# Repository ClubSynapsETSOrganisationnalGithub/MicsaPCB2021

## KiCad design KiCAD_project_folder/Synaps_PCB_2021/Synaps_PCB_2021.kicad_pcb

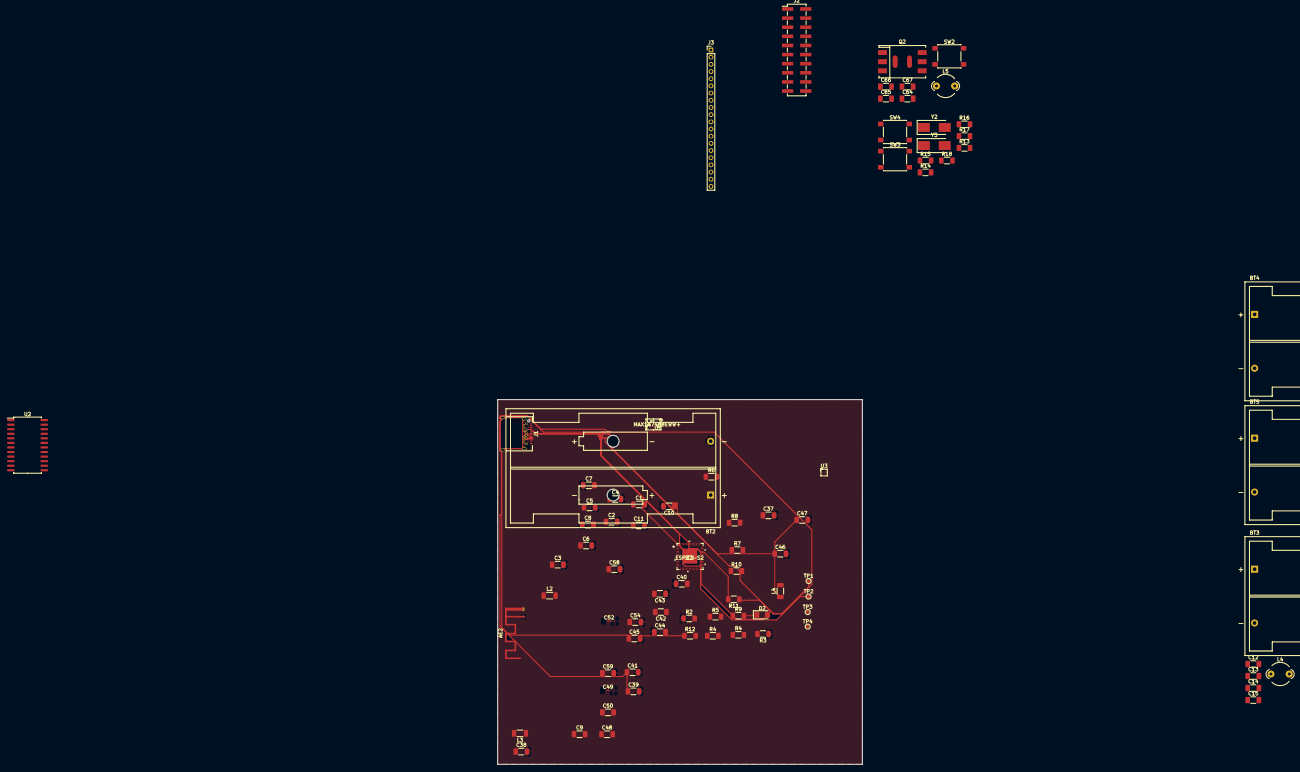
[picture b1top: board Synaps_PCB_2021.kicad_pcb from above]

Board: 4 copper layers, 101.6 x 101.6 mm, 83 parts (0 on the bottom side), 88 nets.

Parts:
AE2: PBC ANT; Texas_SWRA117D_2.4GHz_Left
BT2, BT3, BT4, BT5: Battery_Cell; BatteryHolder_Keystone_2462_2xAA
C1, C6, C40, C44, C45: 1uF; C_1206_3216Metric_Pad1.33x1.80mm_HandSolder
C2, C3, C4, C13, C15, C38, C41, C42, C46, C65, C66: 0.1uF; C_1206_3216Metric_Pad1.33x1.80mm_HandSolder
C5: 100pF; C_1206_3216Metric_Pad1.33x1.80mm_HandSolder
C7, C8: 22pF; C_1206_3216Metric_Pad1.33x1.80mm_HandSolder
C9: 1µF; C_1206_3216Metric_Pad1.33x1.80mm_HandSolder
C10, C11: 0.1uF/50V(10%)(NC); C_1206_3216Metric_Pad1.33x1.80mm_HandSolder
C12, C14, C39, C47, C64, C67: 10uF; C_1206_3216Metric_Pad1.33x1.80mm_HandSolder
C37: 22uF; C_1206_3216Metric_Pad1.33x1.80mm_HandSolder
C43: 3.9nF; C_1206_3216Metric_Pad1.33x1.80mm_HandSolder
C48: 10µF; C_1206_3216Metric_Pad1.33x1.80mm_HandSolder
C49: 19pF; C_01005_0402Metric
C50: 0.1µF; C_1206_3216Metric_Pad1.33x1.80mm_HandSolder
C52: 16pF; C_01005_0402Metric_Pad0.57x0.30mm_HandSolder
C54: NC; C_1206_3216Metric_Pad1.33x1.80mm_HandSolder
C58, C59: 22pF/6.3V(10%); C_1206_3216Metric_Pad1.33x1.80mm_HandSolder
D2: LED; LED_1206_3216Metric_Pad1.42x1.75mm_HandSolder
IC2: ESP32-S2
J1: USB_C_Receptacle; USB_C_Receptacle_Amphenol_12401548E4-2A
J2: Conn_02x10_MountingPin; PinHeader_2x10_P2.54mm_Vertical_SMD
J3: Conn_01x20_MountingPin; PinHeader_1x20_P2.00mm_Vertical
L2: 0.5028nH; L_1206_3216Metric_Pad1.22x1.90mm_HandSolder
L3: 2.0nH; L_1206_3216Metric_Pad1.22x1.90mm_HandSolder
L4, L5: L_Ferrite 60 Omh 1.5 A; LairdTech_28C0236-0JW-10
L4#2: INDUCTOR; L_1206_3216Metric_Pad1.22x1.90mm_HandSolder
Q2: Q_PMOS_DGS; Transformer_NF_ETAL_P2781
R2, R6, R11: 10K; R_1206_3216Metric_Pad1.30x1.75mm_HandSolder
R3: 1M; R_1206_3216Metric_Pad1.30x1.75mm_HandSolder
R4, R4#2, R5, R10, R12: 4.7K; R_1206_3216Metric_Pad1.30x1.75mm_HandSolder
R7, R8, R13, R14, R15, R16: 0; R_1206_3216Metric_Pad1.30x1.75mm_HandSolder
R9: 1K; R_1206_3216Metric_Pad1.30x1.75mm_HandSolder
R17: 499; R_1206_3216Metric_Pad1.30x1.75mm_HandSolder
R18: 10M; R_1206_3216Metric_Pad1.30x1.75mm_HandSolder
SW2, SW3, SW4: SW_Push; SW_Push_1P1T_NO_6x6mm_H9.5mm
TP1: TPCC1; TestPoint_Pad_D1.0mm
TP2: TPCC2; TestPoint_Pad_D1.0mm
TP3: TPCDN; TestPoint_Pad_D1.0mm
TP4: TPCDP; TestPoint_Pad_D1.0mm
U1: MAX14748BEWW+; MAX14748BEWW&plus_
U2: CD74HC4067M; SOIC-24W_7.5x15.4mm_P1.27mm
U3: AT25DF041x-UxN-x; WLCSP-8_1.58x1.63x0.35mm_Layout3x5_P0.35x0.4mm_Ball0.25mm_P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
Y2: 40 MHz; Crystal_SMD_0603-2Pin_6.0x3.5mm_HandSoldering
Y3: 32.768 KHz; Crystal_SMD_0603-2Pin_6.0x3.5mm_HandSoldering

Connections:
+1V1: C2.1, C3.1, C4.1, C5.1, C6.1, C9.1, C37.1, C38.1, C48.1, C50.1, C64.1, C65.1, IC2.1 (VDDA), IC2.20 (VDD3P3_RTC), IC2.27 (VDD3P3_RTC_IO), IC2.45 (VDD3P3_CPU), IC2.51 (VDDA), IC2.54 (VDDA), J3.1, L3.1, L5.1, R4.2, R4#2.2, R5.2, R6.2, R10.1, R12.2, SW2.2, U1.B4 (VTPU), U1.B6 (SYS), U1.B7 (SYS), U1.B8 (SYS), U1.B9 (SYS), U2.24 (VCC)
+5V: C12.1, C13.1, L4.1
/Connectors/CAN_BUS_CLK: IC2.15 (GPIO10), J2.4
/Connectors/CAN_BUS_OFF_ON: IC2.14 (GPIO9), J2.5
/Connectors/CAN_BUS_RX: IC2.12 (GPIO7), J2.2
/Connectors/CAN_BUS_TX: IC2.13 (GPIO8), J2.3
/Connectors/GPIO11: IC2.16 (GPIO11), IC2.28 (GPIO21), J2.15, J2.16
/Connectors/JTAG_MTCK: IC2.43 (MTCK), J2.13
/Connectors/JTAG_MTDI: IC2.47 (MTMS), J2.11
/Connectors/JTAG_MTDO: IC2.44 (MTDO), J2.12
/Connectors/JTAG_MTMS: IC2.46 (MTDI), J2.10
/Connectors/U0RXD: IC2.49 (U0RXD), J2.18
/Connectors/U0TXD: J2.19, R17.2
/Microcontroler/*INT: IC2.7 (GPIO2), R4.1, R4#2.1, R5.1, U1.A3 (SYSOK), U1.D3 (*INT)
/Microcontroler/ADC2_CH1: IC2.18 (GPIO13), IC2.19 (GPIO14)
/Microcontroler/CHIP_BOOT: C10.1, SW3.2
/Microcontroler/CHIP_PU: C11.1, IC2.56 (CHIP_PU), SW4.2
/Microcontroler/DAC_2: IC2.24 (DAC_2), R6.1
/Microcontroler/FSUS: IC2.17 (GPIO12), U1.B2 (FSUS)
/Microcontroler/I2CEXT0_SCL_out: IC2.9 (GPIO4), R10.2, R12.1, U1.C2 (SCL), U1.D2 (SDA)
/Microcontroler/LED_PMIC: D2.2 (A), IC2.11 (GPIO6), R9.1, U1.E2 (LED)
/Microcontroler/LNA_IN: C52.1, IC2.2 (LNA_IN), L2.2
/Microcontroler/SPI3_CLK: IC2.41 (GPIO37), J3.20
/Microcontroler/SPI3_CS0: IC2.40 (GPIO36), U2.10 (S0)
/Microcontroler/SPI3_CS1: IC2.37 (GPIO33), U2.11 (S1)
/Microcontroler/SPI3_CS2: IC2.42 (GPIO38), U2.14 (S2)
/Microcontroler/SPI3_MISO: IC2.38 (GPIO34), U2.1 (COM)
/Microcontroler/SPI3_MOSI: IC2.39 (GPIO35), J3.3
/Microcontroler/SPICLK: R13.2, U3.E1 (SCK)
/Microcontroler/SPICS0: IC2.33 (SPIS0), U3.A3 (~CS)
/Microcontroler/SPID: R7.2, U3.D2 (SI/IO0)
/Microcontroler/SPIQ: R8.2, U3.C3 (SO/IO1)
/Microcontroler/SPIWP: R14.2, U3.E3 (~WP)
/Microcontroler/USB_D+: IC2.26 (GPIO20), J1.A6 (D+), J1.B6 (D+), TP4.1
/Microcontroler/USB_D-: IC2.25 (GPIO19), J1.A7 (D-), J1.B7 (D-), TP3.1
/Microcontroler/VDD3P3: C54.1, IC2.3 (VDD3P3), IC2.4 (VDD3P3), L3.2
/Microcontroler/VDD_SPI: IC2.30 (VDD_SPI), U3.A1 (VCC)
/Microcontroler/XIN: C58.1, R16.2, Y2.1
/Microcontroler/XOUT: C59.1, IC2.52 (XTAL_N)
/Microcontroler/XTAL_32K_N: C8.2, IC2.22 (XTAL_32K_N), R18.2, Y3.2
/Microcontroler/XTAL_32K_P: C7.2, IC2.21 (XTAL32K_P), R18.1, Y3.1
/Microcontroler/XTAL_P: IC2.53 (XTAL_P), R16.1
/Power Supply/CC1: J1.A5 (CC1), TP1.1, U1.D1 (CC1)
/Power Supply/CC2: J1.B5 (CC2), TP2.1
/Power Supply/LX: C42.1, L4#2.2, U1.C6 (LX), U1.C7 (LX), U1.C8 (LX), U1.C9 (LX)
/Power Supply/TPU: R11.2, U1.E3 (THM)
/Power Supply/V_BAT: BT3.1 (+), C39.1, C41.1, SW2.1, U1.A7 (BAT), U1.A8 (BAT), U1.A9 (BAT)
/Probes schematic/SPI_CS_ADC0: J3.4, U2.9 (I0)
/Probes schematic/SPI_CS_ADC1: J3.6, U2.7 (I2)
/Probes schematic/SPI_CS_ADC2: J3.8, U2.5 (I4)
/Probes schematic/SPI_CS_ADC3: J3.10, U2.3 (I6)
/Probes schematic/SPI_CS_ADC4: J3.12, U2.23 (I8)
/Probes schematic/SPI_CS_ADC5: J3.14, U2.21 (I10)
/Probes schematic/SPI_CS_ADC6: J3.16, U2.19 (I12)
/Probes schematic/SPI_CS_ADC7: J3.18, U2.17 (I14)
/Probes schematic/SPI_OUT_ADC0: J3.5, U2.8 (I1)
/Probes schematic/SPI_OUT_ADC1: J3.7, U2.6 (I3)
/Probes schematic/SPI_OUT_ADC2: J3.9, U2.4 (I5)
/Probes schematic/SPI_OUT_ADC3: J3.11, U2.2 (I7)
/Probes schematic/SPI_OUT_ADC4: J3.13, U2.22 (I9)
/Probes schematic/SPI_OUT_ADC5: J3.15, U2.20 (I11)
/Probes schematic/SPI_OUT_ADC6: J3.17, U2.18 (I13)
/Probes schematic/SPI_OUT_ADC7: J3.19, U2.16 (I15)
GNDREF: AE2.1, BT2.2 (-), BT5.2 (-), C1.2, C2.2, C3.2, C4.2, C5.2, C6.2, C7.1, C8.1, C9.2, C10.2, C11.2, C12.2, C13.2, C14.2, C15.2, C37.2, C38.2, C39.2, C40.1, C41.2, C43.1, C44.1, C45.2, C46.2, C47.2, C48.2, C49.2, C50.2, C52.2, C54.2, C58.2, C59.2, C64.2, C65.2, C66.2, C67.2, IC2.57 (EPAD), J1.A1 (GND), J1.A12 (GND), J1.B1 (GND), J1.B12 (GND), J2.1, J2.6, J2.9, J2.14, J2.17, J2.20, J3.2, R2.1, R3.1, SW3.1, SW4.1, U1.B3 (DGND), U1.C4 (GND), U1.D4 (GND), U1.D5 (GND), U1.D6 (PGND), U1.D7 (PGND), U1.D8 (PGND), U1.D9 (PGND), U2.12 (GND), U2.15 (~E), U3.B2 (GND), Y2.2
unnamed: AE2.2, C49.1, L2.1
unnamed: BT2.1 (+), BT3.2 (-)
unnamed: BT4.2 (-), BT5.1 (+)
unnamed: C14.1, C15.1, L4.2
unnamed: C40.2, U1.C3 (VCCINT)
unnamed: C42.2, U1.C5 (BST)
unnamed: C43.2, U1.A5 (COMP)
unnamed: C44.2, U1.B5 (BREG)
unnamed: C45.1, U1.E4 (SFOUT)
unnamed: C46.1, C47.1, L4#2.1, U1.E6 (BYP), U1.E7 (BYP), U1.E8 (BYP), U1.E9 (BYP)
unnamed: D2.1 (K), R9.2
unnamed: IC2.34 (SPICLK), R13.1
unnamed: IC2.36 (SPID), R7.1
unnamed: IC2.31 (SPIHD), R15.1
unnamed: IC2.35 (SPIQ), R8.1
unnamed: IC2.32 (SPIWD), R14.1
unnamed: IC2.48 (U0TXD), R17.1
unnamed: J1.S1 (SHIELD), R3.2
unnamed: Q2.2 (G), U1.F5 (NVP)
unnamed: Q2.3 (S), U1.F6 (CHGIN), U1.F7 (CHGIN), U1.F8 (CHGIN), U1.F9 (CHGIN)
unnamed: R2.2, U1.A6 (SET)
unnamed: R11.1, U1.A4 (TPU)
VAA: C66.1, C67.1, L5.2
VBUS: C1.1, J1.A4 (VBUS), J1.A9 (VBUS), J1.B4 (VBUS), J1.B9 (VBUS)

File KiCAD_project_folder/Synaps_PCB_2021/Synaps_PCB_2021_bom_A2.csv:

Component;Description;Part;References;Value;Footprint;Quantity Per PCB;Datasheet;Supplier Link
1;Dipole antenna;Antenna_Dipole;AE2;PBC ANT;Texas_SWRA117D_2.4GHz_Left;1;~;
2;Single-cell battery;Battery_Cell;BT2;Battery_Cell;BatteryHolder_Keystone_2462_2xAA;1;~;
3;Unpolarized capacitor;C;C7 C8;12.5pF;C_1206_3216Metric_Pad1.33x1.80mm_HandSolder;2;~;
4;Unpolarized capacitor;C;C5;100pF;C_1206_3216Metric_Pad1.33x1.80mm_HandSolder;1;~;
5;Unpolarized capacitor;C;C43;3.9nF;C_1206_3216Metric_Pad1.33x1.80mm_HandSolder;1;~;
6;Unpolarized capacitor;C;C2 C3 C4 C38 C41 C42 C46 C50 C65 C66;0.1uF;C_1206_3216Metric_Pad1.33x1.80mm_HandSolder;10;~;
7;Capacitor symbol for simulation only;CAP;C1;1uF;C_1206_3216Metric_Pad1.33x1.80mm_HandSolder;1;~;
8;Unpolarized capacitor;C;C6 C9 C40 C44 C45;1uF;C_1206_3216Metric_Pad1.33x1.80mm_HandSolder;5;~;
9;Unpolarized capacitor;C;C39 C47 C48 C64 C67;10uF;C_1206_3216Metric_Pad1.33x1.80mm_HandSolder;5;~;
10;Unpolarized capacitor;C;C37;22uF;C_1206_3216Metric_Pad1.33x1.80mm_HandSolder;1;~;
11;Unpolarized capacitor;C;C10 C11;0.1uF/50V(10%)(NC);C_1206_3216Metric_Pad1.33x1.80mm_HandSolder;2;~;
12;Unpolarized capacitor;C;C58 C59;22pF/6.3V(10%);C_1206_3216Metric_Pad1.33x1.80mm_HandSolder;2;~;
13;Unpolarized capacitor;C;C54;NC;C_1206_3216Metric_Pad1.33x1.80mm_HandSolder;1;~;
14;Unpolarized capacitor;C;C49 C52;TBD;C_1206_3216Metric_Pad1.33x1.80mm_HandSolder;2;~;
15;Light emitting diode;LED;D2;LED;LED_1206_3216Metric_Pad1.42x1.75mm_HandSolder;1;~;
16;;ESP32-S2;IC2;ESP32-S2;ESP32-S2;1;;
17;Generic connectable mounting pin connector, single row, 01x20, script generated (kicad-library-utils/schlib/autogen/connector/);Conn_01x20_MountingPin;J2 J3;Conn_01x20_MountingPin;PinHeader_1x20_P2.00mm_Vertical;2;~;
18;USB Full-Featured Type-C Receptacle connector;USB_C_Receptacle;J1;USB_C_Receptacle;USB_C_Receptacle_Amphenol_12401548E4-2A;1;https://www.usb.org/sites/default/files/documents/usb_type-c.zip;
19;Inductor symbol for simulation only;INDUCTOR;L3;2.0nH;L_1206_3216Metric_Pad1.22x1.90mm_HandSolder;1;~;
20;Inductor symbol for simulation only;INDUCTOR;L4;INDUCTOR;L_1206_3216Metric_Pad1.22x1.90mm_HandSolder;1;~;
21;Inductor with ferrite core;L_Ferrite;L5;L_Ferrite;LairdTech_28C0236-0JW-10;1;~;
22;Inductor symbol for simulation only;INDUCTOR;L2;TBD;L_1206_3216Metric_Pad1.22x1.90mm_HandSolder;1;~;
23;P-MOSFET transistor, drain/gate/source;Q_PMOS_DGS;Q2;Q_PMOS_DGS;Transformer_NF_ETAL_P2781;1;~;
24;Resistor, US symbol;R_US;R7 R8 R13 R14 R15 R16;0;R_1206_3216Metric_Pad1.30x1.75mm_HandSolder;6;~;
25;Resistor, US symbol;R_US;R17;499;R_1206_3216Metric_Pad1.30x1.75mm_HandSolder;1;~;
26;Resistor, US symbol;R_US;R9;1K;R_1206_3216Metric_Pad1.30x1.75mm_HandSolder;1;~;
27;Resistor, US symbol;R_US;R4 R5 R10 R12;4.7K;R_1206_3216Metric_Pad1.30x1.75mm_HandSolder;4;~;
28;Resistor, US symbol;R_US;R2 R6 R11;10K;R_1206_3216Metric_Pad1.30x1.75mm_HandSolder;3;~;
29;Resistor, US symbol;R_US;R3;1M;R_1206_3216Metric_Pad1.30x1.75mm_HandSolder;1;~;
30;Resistor, US symbol;R_US;R18;10M;R_1206_3216Metric_Pad1.30x1.75mm_HandSolder;1;~;
31;Push button switch, generic, two pins;SW_Push;SW2 SW3 SW4;SW_Push;SW_Push_1P1T_NO_6x6mm_H9.5mm;3;~;
32;4-Mbit, 1.65V Minimum SPI Serial Flash Memory with Dual-I/O, WLCSP-8;AT25DF041x-UxN-x;U3;AT25DF041x-UxN-x;WLCSP-8_1.58x1.63x0.35mm_Layout3x5_P0.35x0.4mm_Ball0.25mm_Pad0.25mm_NSMD;1;http://www.adestotech.com/wp-content/uploads/DS-AT25DF041B_040.pdf;
33;High-Speed CMOS Logic 16-Channel Analog Multiplexer/Demultiplexer, SOIC-24;CD74HC4067M;U2;CD74HC4067M;SOIC-24W_7.5x15.4mm_P1.27mm;1;http://www.ti.com/lit/ds/symlink/cd74hc4067.pdf;
34;;MAX14748BEWW+;U1;MAX14748BEWW+;MAX14748BEWW&plus_;1;;
35;Two pin crystal;Crystal;Y3;32.768K;Crystal_SMD_0603-2Pin_6.0x3.5mm_HandSoldering;1;~;
36;Four pin crystal, GND on pins 2 and 4;Crystal_GND24;Y2;Crystal_GND24;Crystal_SMD_0603-2Pin_6.0x3.5mm_HandSoldering;1;~;
;;;;;;;;
;;;;;;;;
;;;;;;;;
;;;;;;;;
;;;;;;;;
Component Groups:;36;;;;;;;
Component Count:;70;;;;;;;
Fitted Components:;70;;;;;;;
Number of PCBs:;1;;;;;;;
Total components:;70;;;;;;;
Schematic Version:;A2;;;;;;;
Schematic Date:;2022-06-17;;;;;;;
PCB Variant:;default;;;;;;;
BoM Date:;2022-07-05 18:57:13;;;;;;;
Schematic Source:;Synaps_PCB_2021.kicad_sch;;;;;;;
KiCad Version:;Eeschema (6.0.2);;;;;;;

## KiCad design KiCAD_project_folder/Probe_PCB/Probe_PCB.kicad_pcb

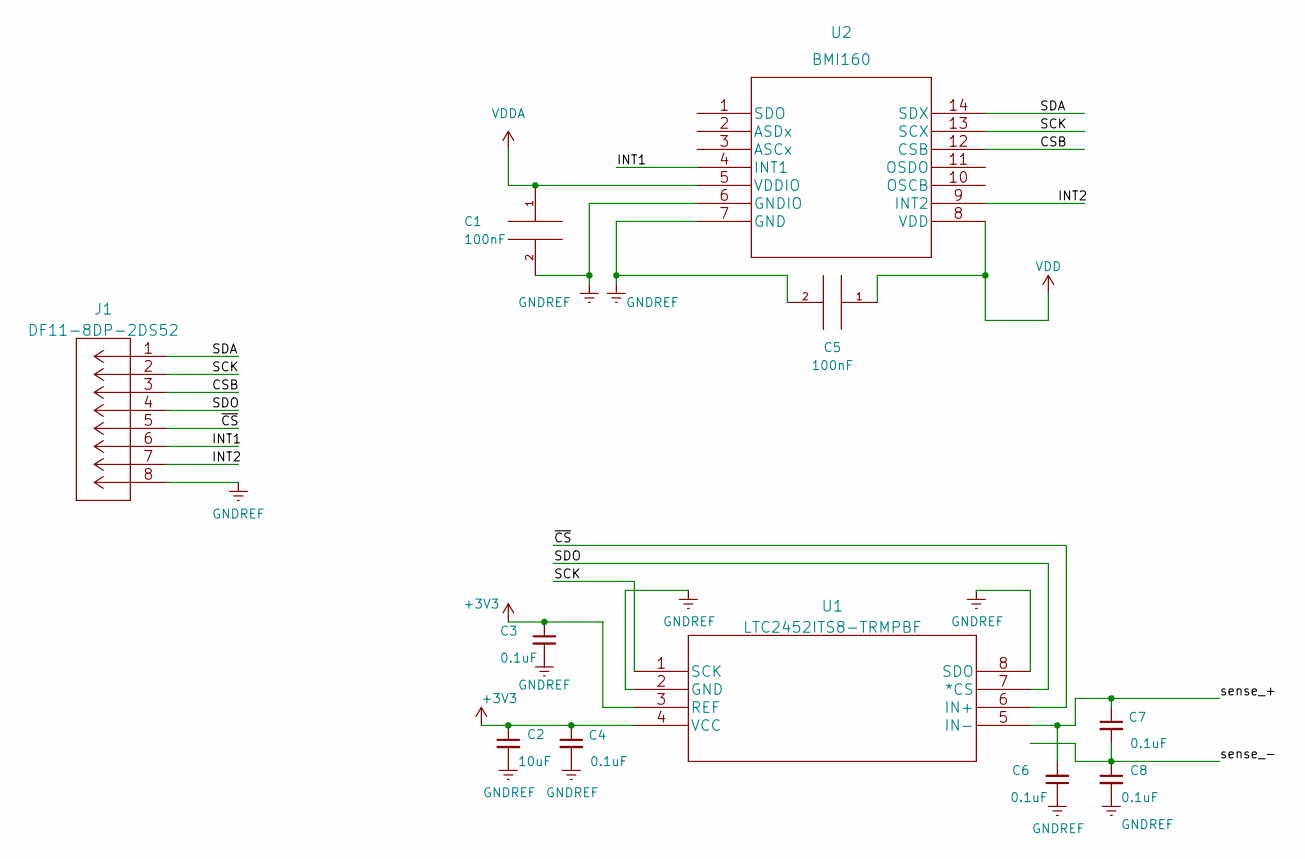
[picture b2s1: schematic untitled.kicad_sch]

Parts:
C1, C5: 100nF; C_1206_3216Metric_Pad1.33x1.80mm_HandSolder
C2: 10uF; C_1206_3216Metric_Pad1.33x1.80mm_HandSolder
C3, C4, C6, C7, C8: 0.1uF; C_1206_3216Metric_Pad1.33x1.80mm_HandSolder
J1: DF11-8DP-2DS52
U1: LTC2452ITS8-TRMPBF
U2: BMI160

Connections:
+3V3: C2.1, C3.1, C4.1, U1.3 (REF), U1.4 (VCC)
/Inertia Measurement Unit & ADC/CSB: J1.3, U2.12 (CSB)
/Inertia Measurement Unit & ADC/INT1: J1.6, U2.4 (INT1)
/Inertia Measurement Unit & ADC/INT2: J1.7, U2.9 (INT2)
/Inertia Measurement Unit & ADC/SCK: J1.2, U1.1 (SCK), U2.13 (SCX)
/Inertia Measurement Unit & ADC/SDA: J1.1, U2.14 (SDX)
/Inertia Measurement Unit & ADC/SDO: J1.4, U1.7 (*CS)
/Inertia Measurement Unit & ADC/sense_+: C6.2, C7.1, U1.5 (IN-)
/Inertia Measurement Unit & ADC/sense_-: C7.2, C8.1
/Inertia Measurement Unit & ADC/~CS: J1.5, U1.6 (IN+)
GNDREF: C1.2, C2.2, C3.2, C4.2, C5.2, C6.1, C8.2, J1.8, U1.2 (GND), U1.8 (SDO), U2.6 (GNDIO), U2.7 (GND)
VDD: C5.1, U2.8 (VDD)
VDDA: C1.1, U2.5 (VDDIO)

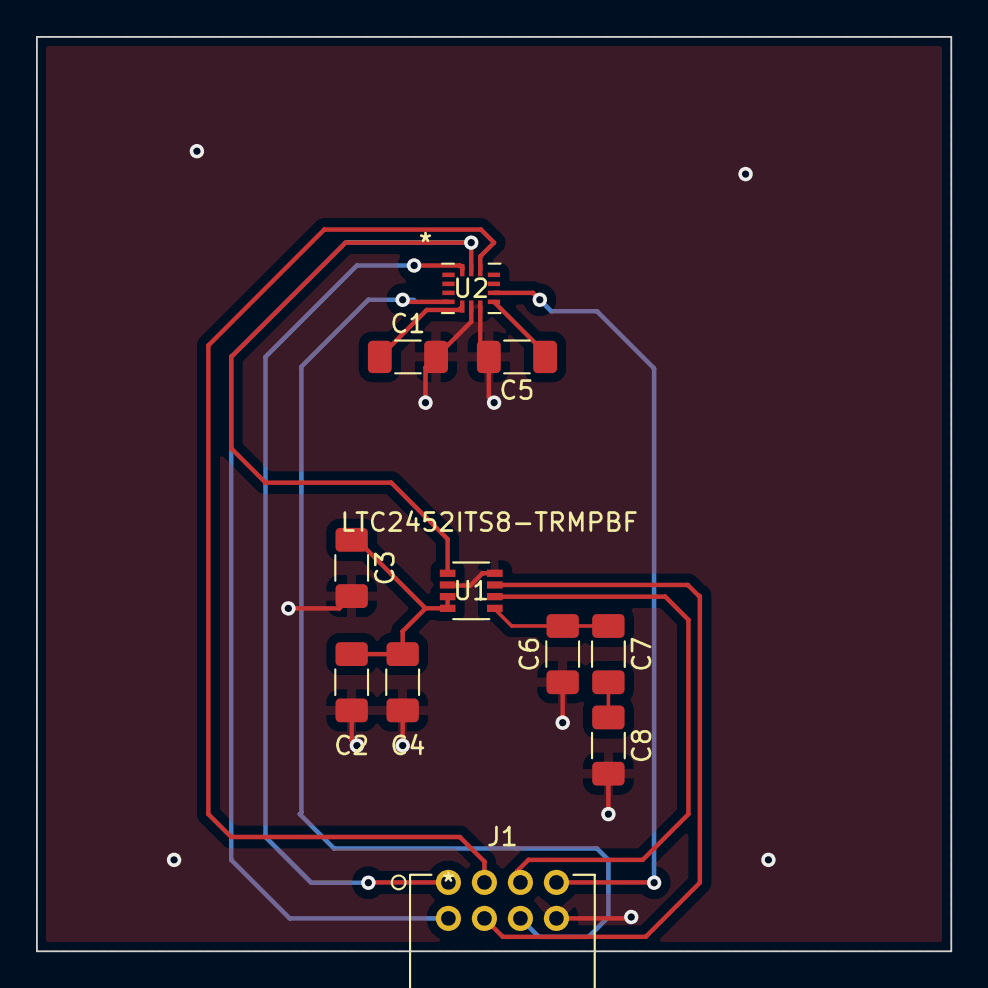
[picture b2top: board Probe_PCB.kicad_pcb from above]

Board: 4 copper layers, 50.8 x 50.8 mm, 11 parts (0 on the bottom side), 13 nets.

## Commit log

2021-11-05 Reworked library folders and added IMUs to project library
2022-03-17 Project refactoring for windows
2022-03-17 Adding Libraries folder to project
2022-03-17 Added library for one piece
2022-03-17 Removed previous sym-lib-table
2022-03-17 Added piece ul_LTC2452ITS8
2022-03-21 Modified gitignore file because wrong type, was blocking lib updates
2022-03-22 Added new library and changement de power ic, old one unavailable
2022-03-24 Modified gitignore file
2022-03-24 Modified git ignore file
2022-03-24 Added LTC2452 librairy
2022-03-24 Inertia measurement unit schematic
2022-03-31 Added basic PCB guidelines
2022-03-31 Showed Myiah how PCB section works
2022-04-05 Added Probe_PCB KiCAD project
2022-04-05 Added draft PCB layout for probe
2022-04-07 Added connector for probe, needs to be routed
2022-04-07 PCB probe modified
2022-05-17 modified the battery file
2022-05-17 Trying to force to reset to previous commit
2022-05-17 Added new ESP32-S2 model
2022-05-17 Added Esp32-S2 datasheet files and hardware design guidelines to project
2022-05-24 Microcontrolling routing and pin assigment
2022-05-25 Worked on schematic for power supply
2022-06-07 Added footprints to powersupply schematic and started placing components on PCB
2022-06-14 Reworking Powersupply
2022-06-14 updated missing annotation
2022-06-14 PCB ucontroller
2022-06-14 Reworded PMIC and probe select
2022-06-16 Redid schematic, fixed wrong setup
2022-06-17 Updated pcb editor with the new components imported
2022-06-18 Fixed Board Setup to be able to trace BGA
2022-06-18 Testing to see with Design Rule Check if saved
2022-06-18 Update schematic sheets and creates image to allow the board setup to be shared
2022-06-18 Testing board setup
2022-06-23 Worked on MAX tracking for PCB
2022-07-05 Fixed missing connections + plus added rough BOM
2022-08-26 Updated BOM and power circuit has to be redone because of missing parts
2022-09-13 updated libraries and added parts for TPS25741
2022-09-21 Added subcomponents for replacement charging circuit
2022-11-28 power supply structure rework
2023-04-17 schematic finished
2023-04-19 added new squeletton for probe pcb
2023-04-26 added schematic for filters and amplifier
2023-05-23 Schematic update
2023-06-19 Transistionned board to ESP32S3, wip
2023-06-19 Trying to push big update

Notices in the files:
parts and their libraries:
Copyright 2021 Accelerated Designs. All rights reserved.
